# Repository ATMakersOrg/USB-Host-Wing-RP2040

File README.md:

# USB-Host-Wing-RP2040
 Prototype of a USB Host Feather Wing using the RP2040
 
 Based on the excellent Feather board by Limor Fried and quite unlikely to work at the moment.  This is just a starting point to see where this could go.  
 
# Goals
 * Board should run TinyUSB (probably through Arduino when that works) to host USB peripherals.
 * Logic on this board would read the USB and then send messages to the main feather via UART (by default) or I2C or SPI with appropriate solder jumpers set
 * Voltage on the USB Host port should be 5V even when the Feather is being powered by a battery, so an onboard boost converter is needed.
 
# Current Challenges
  * Layout is ineffecient (and there are probably conflicts, etc.
  * Room in the center could be used to expose additional GPIO or Analog pins (which would be handy)
  * It would be nice to have second rows of headers to allow connections from GPIO on this wing to the main feather.
  * Power on the USB-C connector is probably wrong... I need to think through how to handle programming vs hosting w/it.
  * The Boost converter I found (PCA9411) has a BGA package which would be hard to solder (and I know nothing about it) - looking to replace with MCP1642B-50 which is easier to solder & seems like a better fit.
  * The MISO and MOSI lines should not be swapped ( need to redo them)
 
 I welcome all input (including thoughts about killing this idea)!
 Bill

NOTE: Images are likely out of date - check out the Eagle Files

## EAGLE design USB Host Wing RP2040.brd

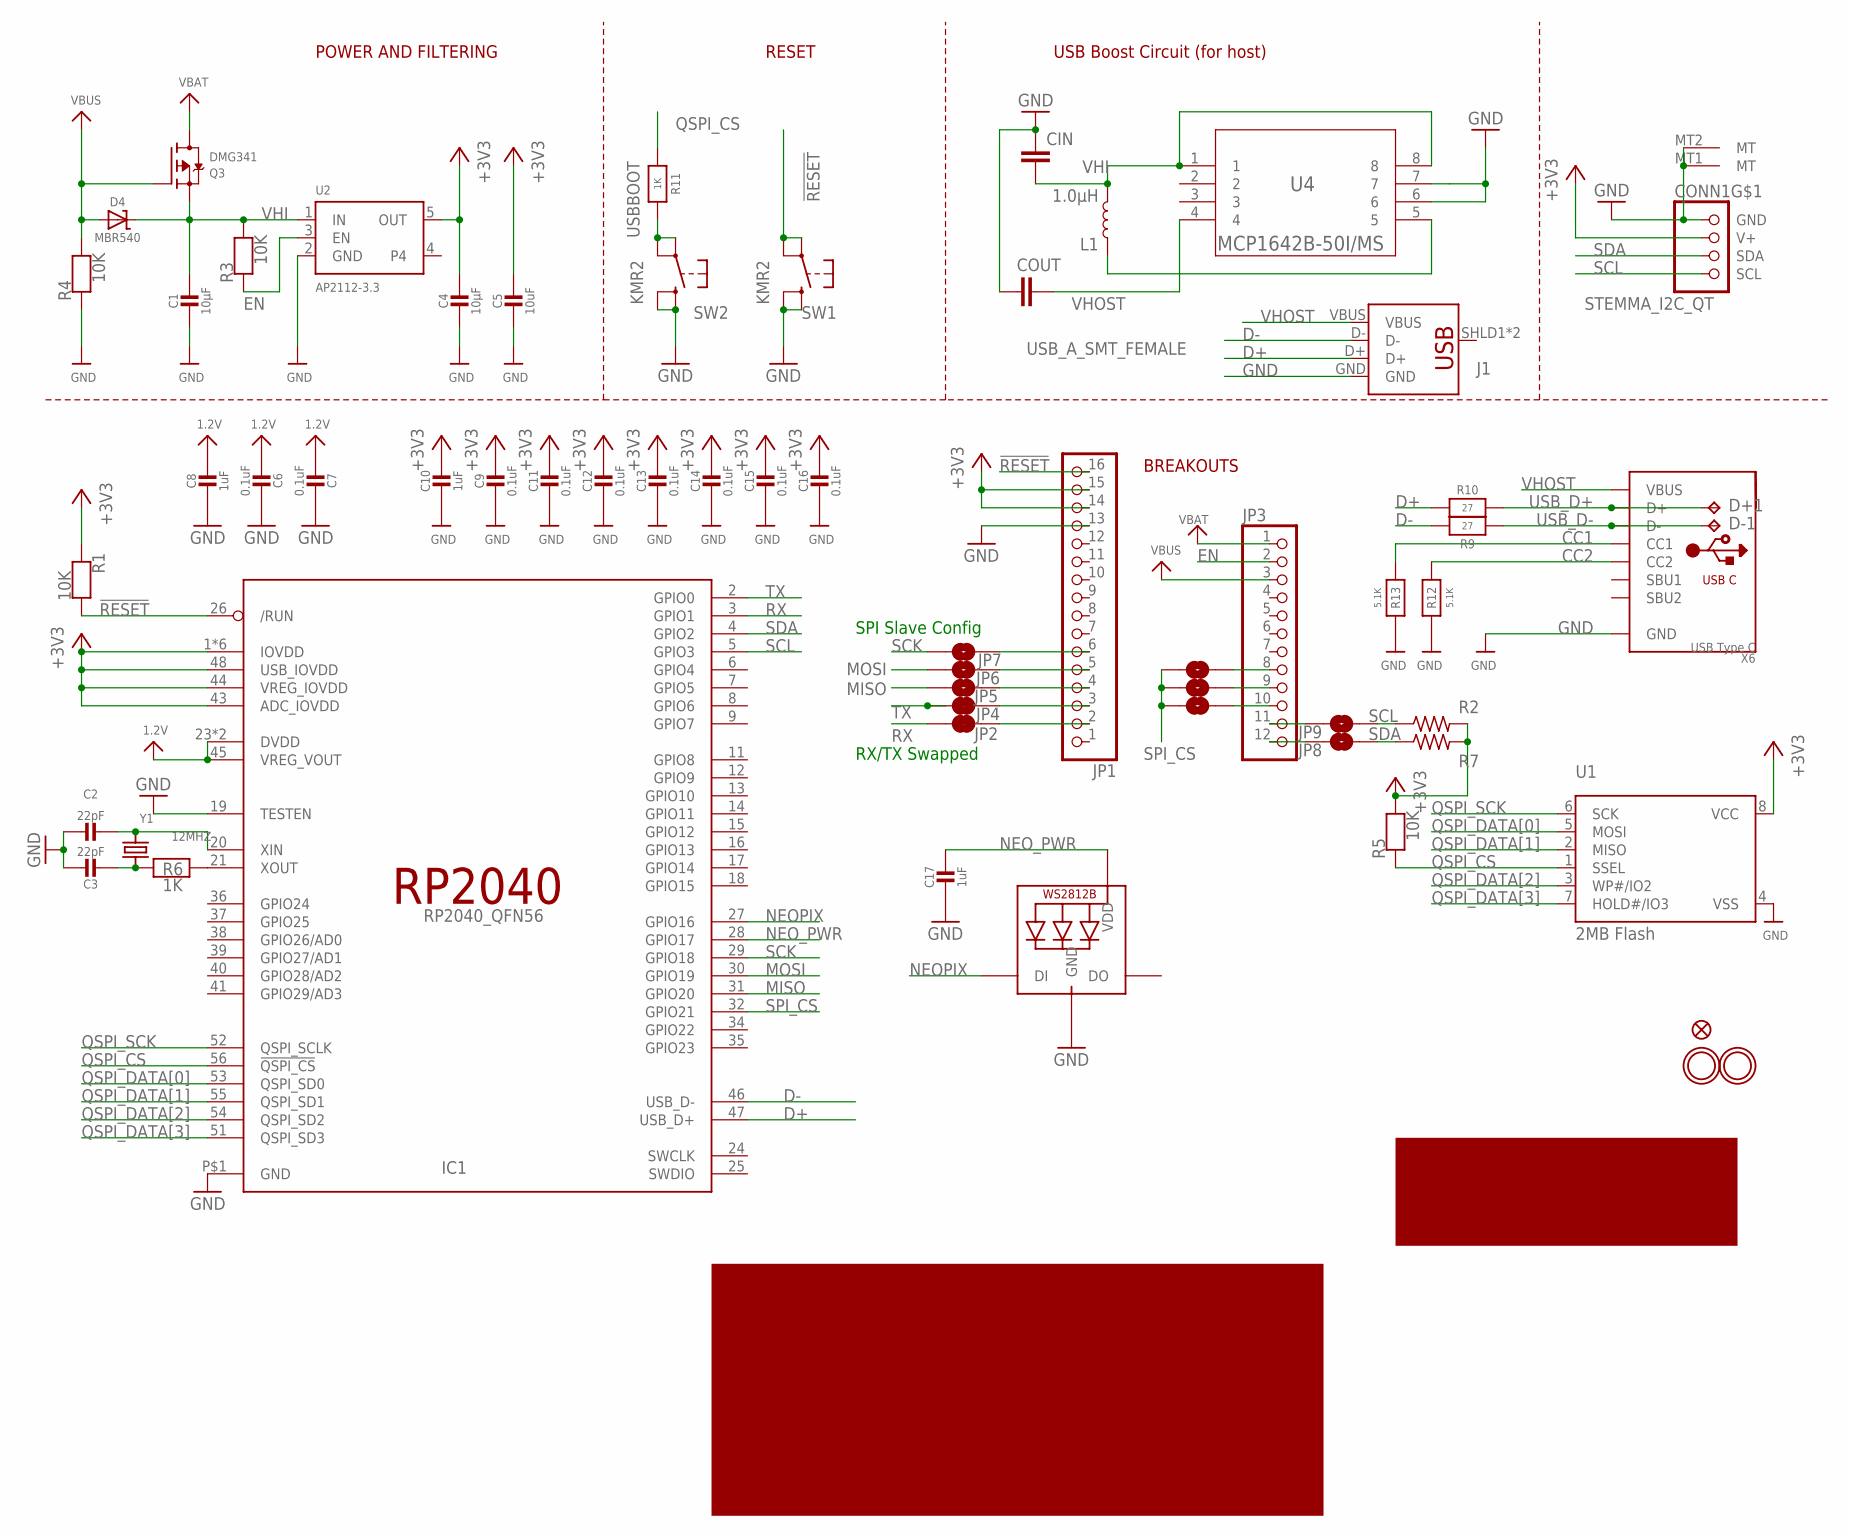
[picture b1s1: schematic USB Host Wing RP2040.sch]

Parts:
C1, C4: 10µF; 0805-NO
C2, C3: 22pF; 0603-NO
C5: 10uF; 0805-NO
C6, C7, C9, C11, C12, C13, C14, C15, C16: 0.1uF; 0603-NO
C8, C10, C17: 1uF; 0603-NO
CIN: SPARKFUN_CAP0603-CAP; SPARKFUN_0603-CAP
CONN1: STEMMA_I2C_QT; JST_SH4
COUT: SPARKFUN_CAP0603-CAP; SPARKFUN_0603-CAP
D4: MBR540; SOD-123
D+1: TPB1,27; B1,27
D-1: TPB1,27; B1,27
IC1: RP2040_QFN56; QFN56_7MM_REDUCEDEPAD
J1: USB_A_SMT_FEMALE; USB-A-S-SILK-FEMALE
JP1: HEADER-1X16ROUND; 1X16_ROUND
JP2, JP4: JUMPER-SMT_2_NC_TRACE_SILK; SMT-JUMPER_2_NC_TRACE_SILK
JP3: HEADER-1X12; 1X12_ROUND
JP5, JP6, JP7, JP8, JP9, JP10, JP11, JP12: JUMPER-SMT_2_NO_SILK; SMT-JUMPER_2_NO_SILK
L1: 1.0μH; 0805-WIDE
LED1: WS2812B3535; LED3535
Q3: DMG341; SOT23-R
R1, R3, R4, R5: 10K; 0603-NO
R2, R7: R-US_R0603; R0603
R6, R11: 1K; 0603-NO
R9, R10: 27; 0603-NO
R12, R13: 5.1K; 0603-NO
SW1, SW2: KMR2; BTN_KMR2_4.6X2.8
U1: 2MB Flash; SOIC8_208MIL
U2: AP2112-3.3; SOT23-5@1
U4: MCP1642B-50I/MS; MSOP8_MCP1642B-50I/MS_MCH
U$31, U$32: MOUNTINGHOLE2.5; MOUNTINGHOLE_2.5_PLATED
U$35: FIDUCIAL_1MM
X6: USB Type C; USB_C_CUSB31-CFM2AX-01-X
Y1: 12MHZ; CRYSTAL_2.5X2

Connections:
1.2V: C6.2, C7.2, C8.1, IC1.23 (DVDD), IC1.45 (VREG_VOUT), IC1.50 (DVDD)
!RESET: IC1.26 (/RUN), JP1.16, R1.2, SW1.A, SW1.A' (P1)
+3V3: C4.1, C5.1, C9.1, C10.1, C11.1, C12.1, C13.1, C14.1, C15.1, C16.1, CONN1.2 (V+), IC1.1 (IOVDD), IC1.10 (IOVDD), IC1.22 (IOVDD), IC1.33 (IOVDD), IC1.42 (IOVDD), IC1.43 (ADC_IOVDD), IC1.44 (VREG_IOVDD), IC1.48 (USB_IOVDD), IC1.49 (IOVDD), JP1.14, JP1.15, R1.1, R2.2, R5.2, R7.2, U1.8 (VCC), U2.5 (OUT)
CC1: R13.2, X6.A5 (CC1)
CC2: R12.2, X6.B5 (CC2)
D+: IC1.47 (USB_D+), J1.D+, R10.2
D-: IC1.46 (USB_D-), J1.D-, R9.2
EN: JP3.2, R3.1, U2.3 (EN)
GND: C1.2, C2.1, C3.1, C4.2, C5.2, C6.1, C7.1, C8.2, C9.2, C10.2, C11.2, C12.2, C13.2, C14.2, C15.2, C16.2, C17.2, CIN.1, CONN1.1 (GND), CONN1.MT1 (MT), CONN1.MT2 (MT), COUT.1, IC1.19 (TESTEN), IC1.P$1 (GND), J1.GND, JP1.13, LED1.4 (GND), R4.1, R12.1, R13.1, SW1.B (S), SW1.B' (S1), SW2.B (S), SW2.B' (S1), U1.4 (VSS), U2.2 (GND), U4.6, U4.7, X6.A1B12 (GND), X6.B1A12 (GND)
MISO: IC1.31 (GPIO20), JP5.1
MOSI: IC1.30 (GPIO19), JP6.1
unnamed: JP1.6, JP7.2
unnamed: JP1.5, JP6.2
unnamed: JP1.4, JP5.2
unnamed: JP1.3, JP4.2
unnamed: C2.2, IC1.20 (XIN), Y1.3 (2)
unnamed: C3.2, R6.1, Y1.1
unnamed: IC1.21 (XOUT), R6.2
unnamed: JP1.2, JP2.2
unnamed: JP3.11, JP9.1
unnamed: L1.1, U4.5
unnamed: JP3.12, JP8.1
unnamed: JP3.8, JP12.2
unnamed: JP3.9, JP11.2
unnamed: JP3.10, JP10.2
NEOPIX: IC1.27 (GPIO16), LED1.1 (DI)
NEO_PWR: C17.1, IC1.28 (GPIO17), LED1.2 (VDD)
QSPI_CS: IC1.56 (!QSPI_CS), R5.1, R11.1, U1.1 (SSEL)
QSPI_DATA[0]: IC1.53 (QSPI_SD0), U1.5 (MOSI)
QSPI_DATA[1]: IC1.55 (QSPI_SD1), U1.2 (MISO)
QSPI_DATA[2]: IC1.54 (QSPI_SD2), U1.3 (WP#/IO2)
QSPI_DATA[3]: IC1.51 (QSPI_SD3), U1.7 (HOLD#/IO3)
QSPI_SCK: IC1.52 (QSPI_SCLK), U1.6 (SCK)
RX: IC1.3 (GPIO1), JP2.1
SCK: IC1.29 (GPIO18), JP7.1
SCL: CONN1.4 (SCL), IC1.5 (GPIO3), JP9.2, R2.1
SDA: CONN1.3 (SDA), IC1.4 (GPIO2), JP8.2, R7.1
SPI_CS: IC1.32 (GPIO21), JP10.1, JP11.1, JP12.1
TX: IC1.2 (GPIO0), JP4.1
USBBOOT: R11.2, SW2.A, SW2.A' (P1)
USB_D+: D+1.TP, R10.1, X6.A6 (D+), X6.B6 (D+)
USB_D-: D-1.TP, R9.1, X6.A7 (D-), X6.B7 (D-)
VBAT: JP3.1, Q3.3 (D)
VBUS: D4.A, JP3.3, Q3.1 (G), R4.2

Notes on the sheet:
POWER AND FILTERING
RESET
USB Boost Circuit (for host)
BREAKOUTS
RX/TX Swapped
SPI Slave Config

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
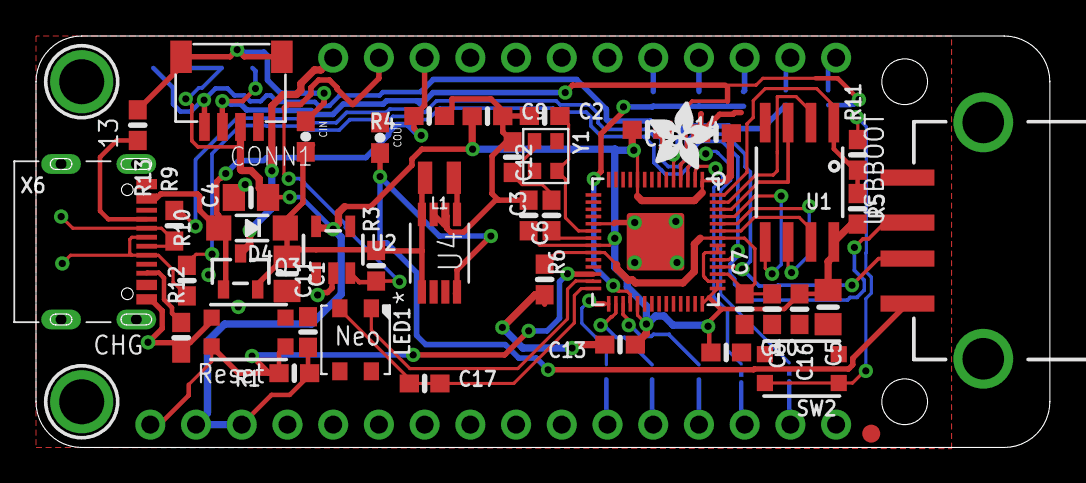
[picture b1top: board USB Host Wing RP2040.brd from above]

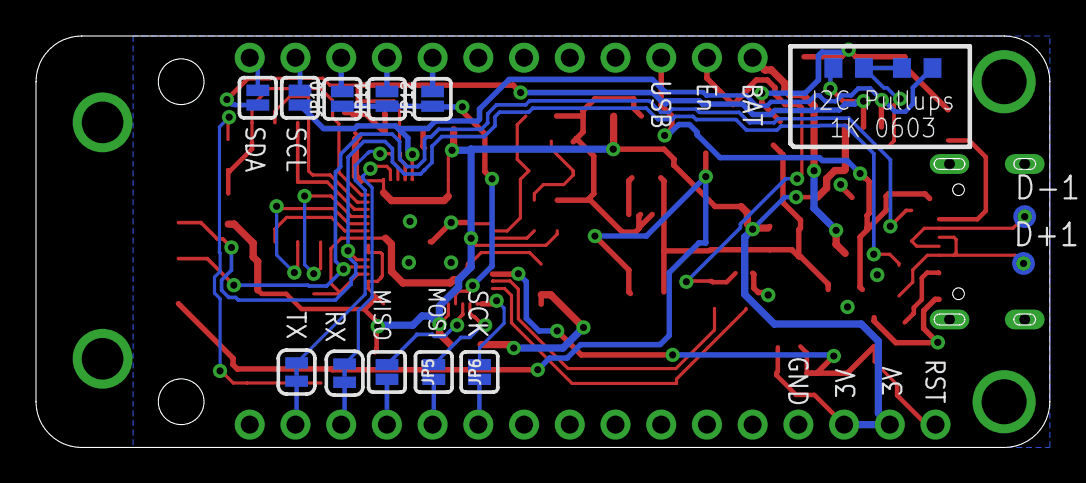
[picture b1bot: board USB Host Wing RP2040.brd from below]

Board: 2 copper layers, 56.3 x 22.9 mm, 63 parts (14 on the bottom side), 46 nets.

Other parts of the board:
U$28: ADAFRUIT_3.5MM

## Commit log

2021-01-22 Adding Images
2021-01-26 Continued fixes
    Modified to replace the boost converter and fix the MOSI/MISO issue. Also added CS jumpers for SPI users.
    Still has air wires & issues.
2021-01-26 Update for John
2021-01-27 Changed source of linear regulator to VHOST

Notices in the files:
parts and their libraries:
microbuilder: This work is placed in the public domain, and may be freely used for commercial and non-commercial work with the following conditions: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
SparkFun-Connectors: Licensing: Creative Commons ShareAlike 4.0 International - https://creativecommons.org/licenses/by-sa/4.0
